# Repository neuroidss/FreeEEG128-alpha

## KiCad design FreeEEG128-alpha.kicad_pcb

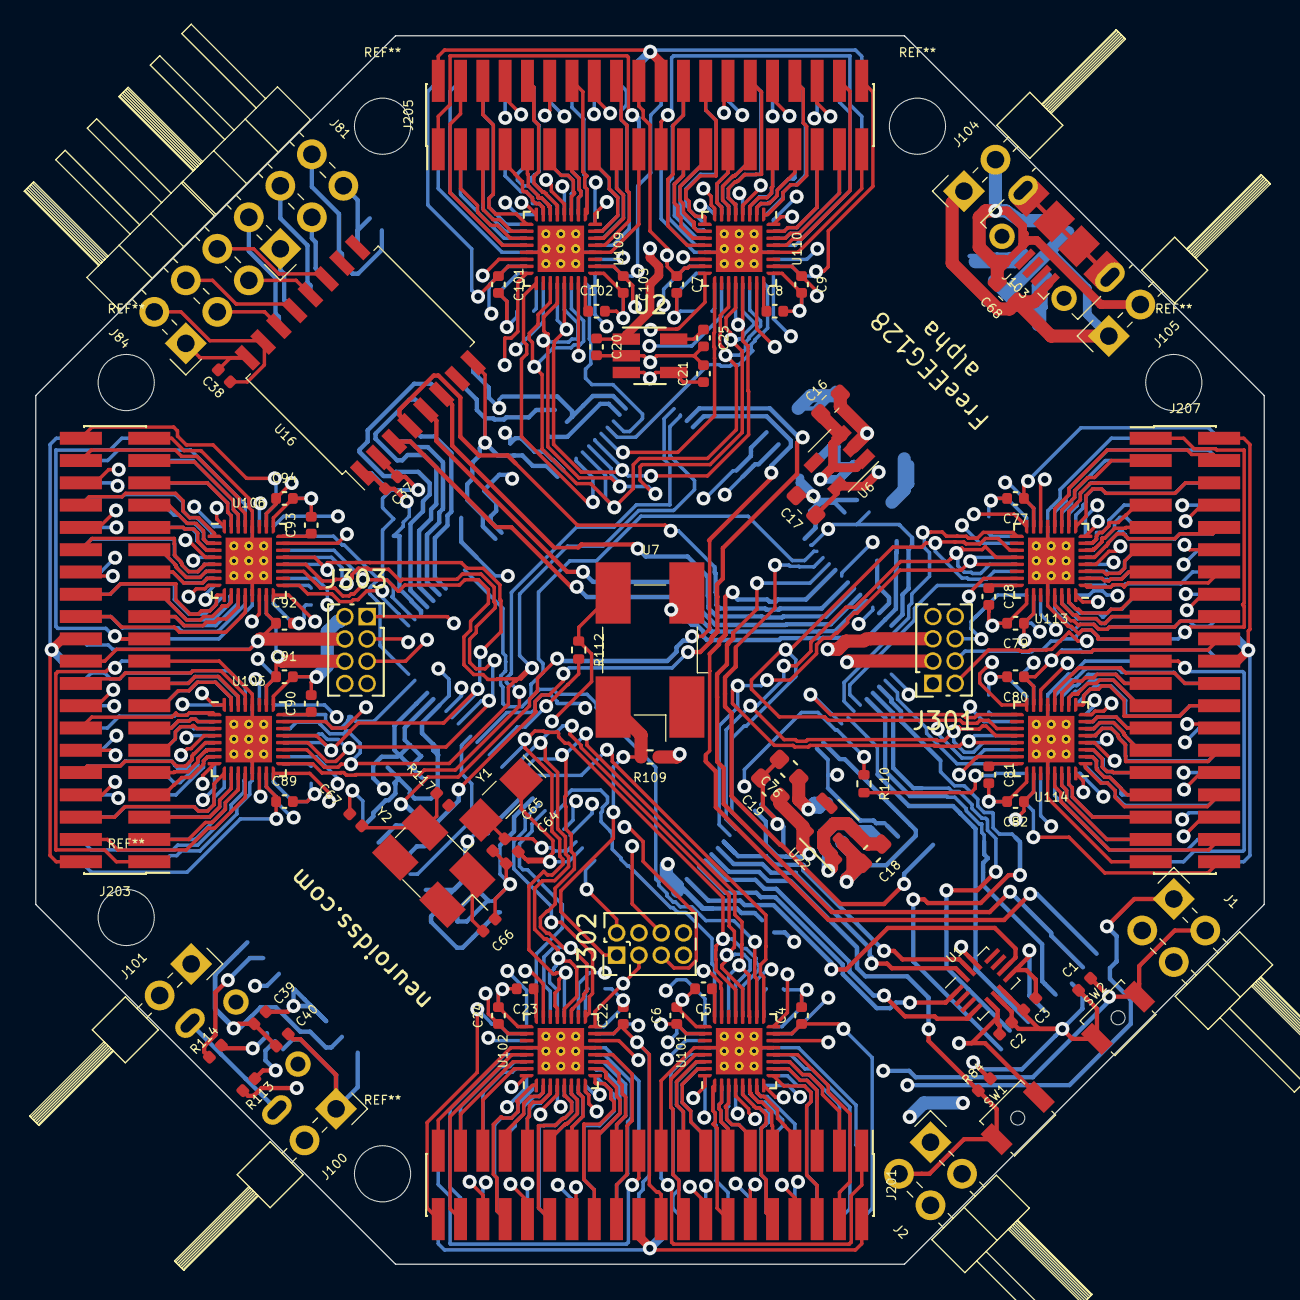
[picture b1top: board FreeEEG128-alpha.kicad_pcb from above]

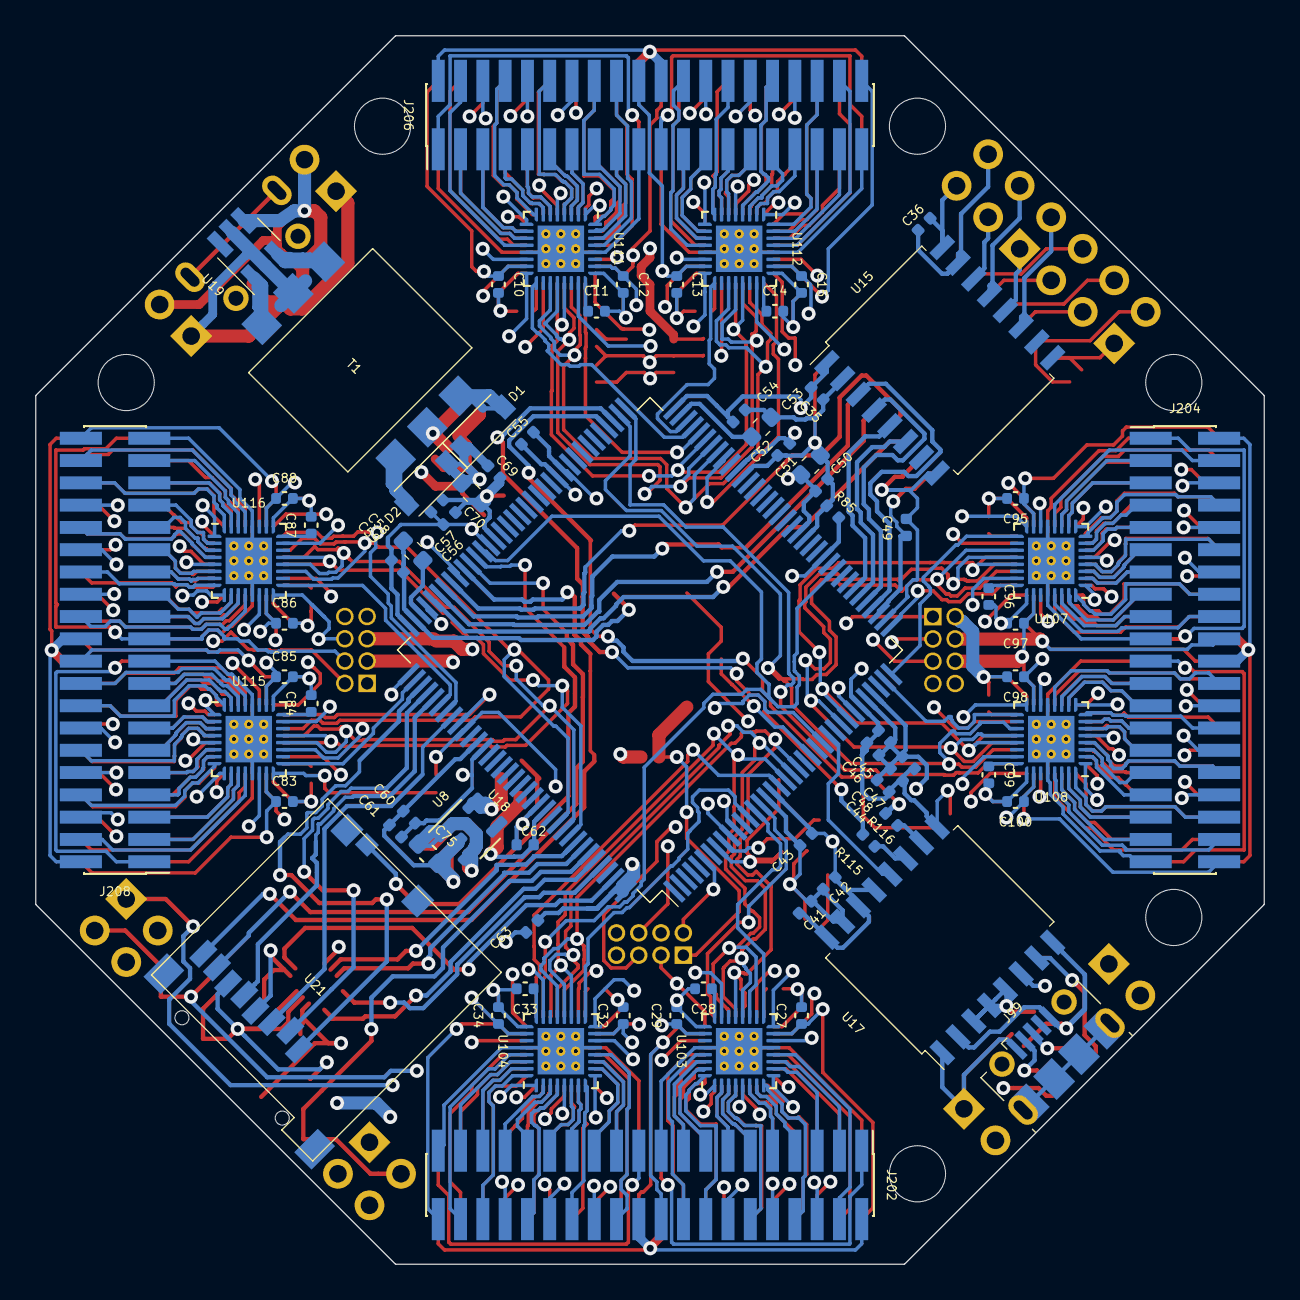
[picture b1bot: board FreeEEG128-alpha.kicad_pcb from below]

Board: 4 copper layers, 70.0 x 70.0 mm, 162 parts (77 on the bottom side), 379 nets.

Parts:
C1, C2, C3, C20, C21, C25, C35, C36, C37, C38, C39, C40, C41, C42, C43, C44, C45, C47, C49, C50, C52, C54, C55, C56, C59, C60, C62, C63, C69: 100n; C_0402_1005Metric
C4, C6, C7, C9, C10, C12, C13, C15, C22, C24, C27, C29, C32, C34, C46, C48, C57, C61, C77, C79, C80, C82, C83, C85, C86, C88, C89, C91, C92, C94, C95, C97, C98, C100, C101, C103: 1u; C_0402_1005Metric
C5, C8, C11, C14, C23, C28, C33, C78, C81, C84, C87, C90, C93, C96, C99, C102: 220nF; C_0402_1005Metric
C16, C17, C18, C19, C53, C58, C75, C76: 2.2u; C_0603_1608Metric
C51: 4.7u; C_0603_1608Metric
C64, C66: CL1; C_0402_1005Metric
C65, C67: CL2; C_0402_1005Metric
C68, C70: 10u; C_0603_1608Metric
D1, D2: D_Schottky; D_SOD-123
J1, J2: Conn_02x02_Odd_Even; PinHeader_2x02_P2.54mm_Horizontal
J81, J84: Conn_02x03_Odd_Even; PinHeader_2x03_P2.54mm_Horizontal
J99, J103: USB_B_Micro; USB_Micro-B_Molex-105017-0001
J100, J101, J104, J105: Conn_01x02; PinHeader_2x01_P2.54mm_Horizontal
J201, J202, J203, J204, J205, J206, J207, J208: Conn_02x20_Odd_Even; PinHeader_2x20_P1.27mm_Vertical_SMD
J301, J303: Conn_02x04_Odd_Even; PinSocket_2x04_P1.27mm_Vertical
J302: Conn_02x04_Odd_Even; PinHeader_2x04_P1.27mm_Vertical
R84, R85: 4k7; R_0402_1005Metric
R109, R110, R112: 0; R_0402_1005Metric
R113, R114, R115, R116: 24; R_0402_1005Metric
R117: R_EXT; R_0402_1005Metric
SW1, SW2: SW_Push; SW_SPST_B3U-1000P-B
T1: 750315371
U1: LSM6DS3; Bosch_LGA-14_3x2.5mm_P0.5mm
U2: REF2025; SOT-23-5_HandSoldering
U6, U8, U22: LP5907; SOT-23-5
U7: FXO-SM7_OSC-SMD7050_short; Oscillator_SMD_EuroQuartz_XO91-4Pin_7.0x5.0mm_HandSoldering
U15: ISO7341c; SOIC-16W_7.5x10.3mm_P1.27mm
U16: ADUM1402BRWZ; SOIC-16W_7.5x10.3mm_P1.27mm
U17: ADuM3160; SOIC-16W_7.5x10.3mm_P1.27mm
U18: STM32H743ZITx; LQFP-144_20x20mm_P0.5mm
U19: SN6505B; SOT-23-6_Handsoldering
U21: 473521001
U101, U102, U103, U104, U105, U106, U107, U108, U109, U110, U111, U112, U113, U114, U115, U116: ADS131M08IRSN; QFN-32-1EP_4x4mm_P0.4mm_EP2.65x2.65mm_ThermalVias
Y1: 32768Hz; Crystal_SMD_EuroQuartz_EQ161-2Pin_3.2x1.5mm_HandSoldering
Y2: 16MHz; Crystal_SMD_EuroQuartz_MJ-4Pin_5.0x3.2mm_HandSoldering

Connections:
/ADC1/24_CAP: C5.1, U101.24 (CAP)
/ADC2/24_CAP: C23.1, U102.24 (CAP)
/ADC3/24_CAP: C28.1, U103.24 (CAP)
/ADC4/24_CAP: C33.1, U104.24 (CAP)
/ADC5/24_CAP: C90.1, U105.24 (CAP)
/ADC6/24_CAP: C93.1, U106.24 (CAP)
/ADC7/24_CAP: C96.1, U107.24 (CAP)
/ADC8/24_CAP: C99.1, U108.24 (CAP)
/ADC9/24_CAP: C102.1, U109.24 (CAP)
/ADC10/24_CAP: C8.1, U110.24 (CAP)
/ADC11/24_CAP: C11.1, U111.24 (CAP)
/ADC12/24_CAP: C14.1, U112.24 (CAP)
/ADC13/24_CAP: C78.1, U113.24 (CAP)
/ADC14/24_CAP: C81.1, U114.24 (CAP)
/ADC15/24_CAP: C84.1, U115.24 (CAP)
/ADC16/24_CAP: C87.1, U116.24 (CAP)
/MCU/8_PC14: C64.1, U18.8 (PC14), Y1.1
/MCU/9_PC15: C65.1, U18.9 (PC15), Y1.2
/MCU/71_VCAP_1: C53.1, U18.71 (VCAP1)
/MCU/106_VCAP_2: C58.1, U18.106 (VCAP2)
ACC_1_SDO_SAO: U1.1 (SDO/SA0), U18.140 (PB9)
ACC_4_INT1: U1.4 (INT1), U18.139 (PB8)
ACC_6_GND: C1.1, C2.2, C3.2, C4.2, C5.2, C6.2, C7.2, C8.2, C9.2, C10.2, C11.2, C12.2, C13.2, C14.2, C15.2, C16.2, C17.2, C18.2, C19.2, C20.2, C21.2, C22.2, C23.2, C24.2, C25.2, C27.2, C28.2, C29.2, C32.2, C33.2, C34.2, C35.2, C37.2, C41.2, C42.2, C43.2, C44.2, C45.2, C46.2, C47.2, C48.2, C49.2, C50.2, C51.2, C52.2, C53.2, C54.2, C55.2, C56.2, C57.2, C58.2, C59.2, C60.2, C61.2, C62.2, C63.2, C64.2, C65.2, C66.2, C67.2, C69.2, C70.2, C75.2, C76.2, C77.2, C78.2, C79.2, C80.2, C81.2, C82.2, C83.2, C84.2, C85.2, C86.2, C87.2, C88.2, C89.2, C90.2, C91.2, C92.2, C93.2, C94.2, C95.2, C96.2, C97.2, C98.2, C99.2, C100.2, C101.2, C102.2, C103.2, J2.2, J201.19, J201.39, J202.19, J202.39, J203.19, J203.39, J204.19, J204.39, J205.19, J205.39, J206.19, J206.39, J207.19, J207.39, J208.19, J208.39, J301.1, J303.2, R84.2, R85.2, SW2.1, T1.5, U1.6 (GND), U1.7 (GND), U2.2 (GND), U6.2 (GND), U7.2 (GND), U8.2 (GND), U15.2 (GND1), U15.8 (GND1), U16.2 (GND1), U16.8 (GND1), U17.9 (GND2), U17.15 (GND2), U18.16 (VSS), U18.31 (VSSA), U18.38 (VSS), U18.51 (VSS), U18.61 (VSS), U18.83 (VSS), U18.94 (VSS), U18.107 (VSS), U18.120 (VSS), U18.130 (VSS), U21.6 (Vss), U22.2 (GND), U101.13 (AGND), U101.25 (DGND), U101.28 (AGND), U101.33 (Thermal_pad), U102.13 (AGND), U102.25 (DGND), U102.28 (AGND), U102.33 (Thermal_pad), U103.13 (AGND), U103.25 (DGND), U103.28 (AGND), U103.33 (Thermal_pad), U104.13 (AGND), U104.25 (DGND), U104.28 (AGND), U104.33 (Thermal_pad), U105.13 (AGND), U105.25 (DGND), U105.28 (AGND), U105.33 (Thermal_pad), U106.13 (AGND), U106.25 (DGND), U106.28 (AGND), U106.33 (Thermal_pad), U107.13 (AGND), U107.25 (DGND), U107.28 (AGND), U107.33 (Thermal_pad), U108.13 (AGND), U108.25 (DGND), U108.28 (AGND), U108.33 (Thermal_pad), U109.13 (AGND), U109.25 (DGND), U109.28 (AGND), U109.33 (Thermal_pad), U110.13 (AGND), U110.25 (DGND), U110.28 (AGND), U110.33 (Thermal_pad), U111.13 (AGND), U111.25 (DGND), U111.28 (AGND), U111.33 (Thermal_pad), U112.13 (AGND), U112.25 (DGND), U112.28 (AGND), U112.33 (Thermal_pad), U113.13 (AGND), U113.25 (DGND), U113.28 (AGND), U113.33 (Thermal_pad), U114.13 (AGND), U114.25 (DGND), U114.28 (AGND), U114.33 (Thermal_pad), U115.13 (AGND), U115.25 (DGND), U115.28 (AGND), U115.33 (Thermal_pad), U116.13 (AGND), U116.25 (DGND), U116.28 (AGND), U116.33 (Thermal_pad)
ACC_9_INT2: U1.9 (INT2), U18.142 (PE1)
ACC_12_CS: C2.1, C3.1, C19.1, C35.1, C37.1, C41.1, C42.1, C43.1, C44.1, C45.1, C46.1, C47.1, C48.1, C49.1, C50.1, C51.1, C52.1, C54.1, C55.1, C56.1, C57.1, C59.1, C60.1, C61.1, C62.1, C63.1, J2.1, J301.5, J302.2, R109.1, SW1.1, U1.5 (VDDIO), U1.8 (VDD), U1.12 (CS), U15.1 (VCC1), U16.1 (VCC1), U17.13 (SPD), U17.14 (VDD2), U17.16 (VBUS2), U18.6 (VBAT), U18.17 (VDD), U18.30 (VDD), U18.32 (VREF+), U18.33 (VDDA), U18.39 (VDD), U18.52 (VDD), U18.62 (VDD), U18.72 (VDD), U18.84 (VDD), U18.95 (VDD33_USB), U18.108 (VDD), U18.121 (VDD), U18.131 (VDD), U18.143 (PDR_ON), U18.144 (VDD), U21.4 (VDD), U22.5 (OUT)
ACC_13_SCL: U1.13 (SCL), U18.136 (PB6)
ACC_14_SDA: U1.14 (SDA), U18.137 (PB7)
ADC1_01_AIN2P: J201.14, U101.1 (AIN2P)
ADC1_02_AIN2N: J201.13, U101.2 (AIN2N)
ADC1_03_AIN3N: J201.11, U101.3 (AIN3N)
ADC1_04_AIN3P: J201.12, U101.4 (AIN3P)
ADC1_05_AIN4P: J201.10, U101.5 (AIN4P)
ADC1_06_AIN4N: J201.9, U101.6 (AIN4N)
ADC1_07_AIN5N: J201.7, U101.7 (AIN5N)
ADC1_08_AIN5P: J201.8, U101.8 (AIN5P)
ADC1_09_AIN6P: J201.6, U101.9 (AIN6P)
ADC1_10_AIN6N: J201.5, U101.10 (AIN6N)
ADC1_11_AIN7N: J201.3, U101.11 (AIN7N)
ADC1_12_AIN7P: J201.4, U101.12 (AIN7P)
ADC1_17_CS: U18.18 (PF6), U101.17 (CS)
ADC1_18_DRDY: U18.46 (PB0), U18.96 (PC6), U101.18 (DRDY)
ADC1_19_SCLK: U18.19 (PF7), U101.19 (SCLK), U102.19 (SCLK), U103.19 (SCLK), U104.19 (SCLK)
ADC1_20_DOUT: U18.20 (PF8), U101.20 (DOUT), U102.20 (DOUT), U103.20 (DOUT), U104.20 (DOUT)
ADC1_21_DIN: U18.21 (PF9), U101.21 (DIN), U102.21 (DIN), U103.21 (DIN), U104.21 (DIN)
ADC1_29_AIN0P: J201.18, U101.29 (AIN0P)
ADC1_30_AIN0N: J201.17, U101.30 (AIN0N)
ADC1_31_AIN1N: J201.15, U101.31 (AIN1N)
ADC1_32_AIN1P: J201.16, U101.32 (AIN1P)
ADC2_01_AIN2P: J201.34, U102.1 (AIN2P)
ADC2_02_AIN2N: J201.33, U102.2 (AIN2N)
ADC2_03_AIN3N: J201.31, U102.3 (AIN3N)
ADC2_04_AIN3P: J201.32, U102.4 (AIN3P)
ADC2_05_AIN4P: J201.30, U102.5 (AIN4P)
ADC2_06_AIN4N: J201.29, U102.6 (AIN4N)
ADC2_07_AIN5N: J201.27, U102.7 (AIN5N)
ADC2_08_AIN5P: J201.28, U102.8 (AIN5P)
ADC2_09_AIN6P: J201.26, U102.9 (AIN6P)
ADC2_10_AIN6N: J201.25, U102.10 (AIN6N)
ADC2_11_AIN7N: J201.23, U102.11 (AIN7N)
ADC2_12_AIN7P: J201.24, U102.12 (AIN7P)
ADC2_17_CS: U18.15 (PF5), U102.17 (CS)
ADC2_29_AIN0P: J201.38, U102.29 (AIN0P)
ADC2_30_AIN0N: J201.37, U102.30 (AIN0N)
ADC2_31_AIN1N: J201.35, U102.31 (AIN1N)
ADC2_32_AIN1P: J201.36, U102.32 (AIN1P)
ADC3_01_AIN2P: J202.14, U103.1 (AIN2P)
ADC3_02_AIN2N: J202.13, U103.2 (AIN2N)
ADC3_03_AIN3N: J202.11, U103.3 (AIN3N)
ADC3_04_AIN3P: J202.12, U103.4 (AIN3P)
ADC3_05_AIN4P: J202.10, U103.5 (AIN4P)
ADC3_06_AIN4N: J202.9, U103.6 (AIN4N)
ADC3_07_AIN5N: J202.7, U103.7 (AIN5N)
ADC3_08_AIN5P: J202.8, U103.8 (AIN5P)
ADC3_09_AIN6P: J202.6, U103.9 (AIN6P)
ADC3_10_AIN6N: J202.5, U103.10 (AIN6N)
ADC3_11_AIN7N: J202.3, U103.11 (AIN7N)
ADC3_12_AIN7P: J202.4, U103.12 (AIN7P)
ADC3_17_CS: U18.14 (PF4), U103.17 (CS)
ADC3_29_AIN0P: J202.18, U103.29 (AIN0P)
ADC3_30_AIN0N: J202.17, U103.30 (AIN0N)
ADC3_31_AIN1N: J202.15, U103.31 (AIN1N)
ADC3_32_AIN1P: J202.16, U103.32 (AIN1P)
ADC4_01_AIN2P: J202.34, U104.1 (AIN2P)
ADC4_02_AIN2N: J202.33, U104.2 (AIN2N)
ADC4_03_AIN3N: J202.31, U104.3 (AIN3N)
ADC4_04_AIN3P: J202.32, U104.4 (AIN3P)
ADC4_05_AIN4P: J202.30, U104.5 (AIN4P)
ADC4_06_AIN4N: J202.29, U104.6 (AIN4N)
ADC4_07_AIN5N: J202.27, U104.7 (AIN5N)
ADC4_08_AIN5P: J202.28, U104.8 (AIN5P)
ADC4_09_AIN6P: J202.26, U104.9 (AIN6P)
ADC4_10_AIN6N: J202.25, U104.10 (AIN6N)
ADC4_11_AIN7N: J202.23, U104.11 (AIN7N)
ADC4_12_AIN7P: J202.24, U104.12 (AIN7P)
ADC4_17_CS: U18.13 (PF3), U104.17 (CS)
ADC4_29_AIN0P: J202.38, U104.29 (AIN0P)
ADC4_30_AIN0N: J202.37, U104.30 (AIN0N)
ADC4_31_AIN1N: J202.35, U104.31 (AIN1N)
ADC4_32_AIN1P: J202.36, U104.32 (AIN1P)
ADC5_01_AIN2P: J203.14, U105.1 (AIN2P)
ADC5_02_AIN2N: J203.13, U105.2 (AIN2N)
ADC5_03_AIN3N: J203.11, U105.3 (AIN3N)
ADC5_04_AIN3P: J203.12, U105.4 (AIN3P)
ADC5_05_AIN4P: J203.10, U105.5 (AIN4P)
ADC5_06_AIN4N: J203.9, U105.6 (AIN4N)
ADC5_07_AIN5N: J203.7, U105.7 (AIN5N)
ADC5_08_AIN5P: J203.8, U105.8 (AIN5P)
ADC5_09_AIN6P: J203.6, U105.9 (AIN6P)
ADC5_10_AIN6N: J203.5, U105.10 (AIN6N)
ADC5_11_AIN7N: J203.3, U105.11 (AIN7N)
ADC5_12_AIN7P: J203.4, U105.12 (AIN7P)
ADC5_17_CS: U18.73 (PB12), U105.17 (CS)
ADC5_19_SCLK: U18.74 (PB13), U105.19 (SCLK), U106.19 (SCLK), U107.19 (SCLK), U108.19 (SCLK)
ADC5_20_DOUT: U18.28 (PC2_C), U105.20 (DOUT), U106.20 (DOUT), U107.20 (DOUT), U108.20 (DOUT)
ADC5_21_DIN: U18.29 (PC3_C), U105.21 (DIN), U106.21 (DIN), U107.21 (DIN), U108.21 (DIN)
ADC5_29_AIN0P: J203.18, U105.29 (AIN0P)
ADC5_30_AIN0N: J203.17, U105.30 (AIN0N)
ADC5_31_AIN1N: J203.15, U105.31 (AIN1N)
ADC5_32_AIN1P: J203.16, U105.32 (AIN1P)
ADC6_01_AIN2P: J203.34, U106.1 (AIN2P)
ADC6_02_AIN2N: J203.33, U106.2 (AIN2N)
ADC6_03_AIN3N: J203.31, U106.3 (AIN3N)
ADC6_04_AIN3P: J203.32, U106.4 (AIN3P)
ADC6_05_AIN4P: J203.30, U106.5 (AIN4P)
ADC6_06_AIN4N: J203.29, U106.6 (AIN4N)
ADC6_07_AIN5N: J203.27, U106.7 (AIN5N)
ADC6_08_AIN5P: J203.28, U106.8 (AIN5P)
ADC6_09_AIN6P: J203.26, U106.9 (AIN6P)
ADC6_10_AIN6N: J203.25, U106.10 (AIN6N)
ADC6_11_AIN7N: J203.23, U106.11 (AIN7N)
ADC6_12_AIN7P: J203.24, U106.12 (AIN7P)
ADC6_17_CS: U18.37 (PA3), U106.17 (CS)
ADC6_29_AIN0P: J203.38, U106.29 (AIN0P)
ADC6_30_AIN0N: J203.37, U106.30 (AIN0N)
ADC6_31_AIN1N: J203.35, U106.31 (AIN1N)
ADC6_32_AIN1P: J203.36, U106.32 (AIN1P)
ADC7_01_AIN2P: J204.14, U107.1 (AIN2P)
ADC7_02_AIN2N: J204.13, U107.2 (AIN2N)
ADC7_03_AIN3N: J204.11, U107.3 (AIN3N)
ADC7_04_AIN3P: J204.12, U107.4 (AIN3P)
ADC7_05_AIN4P: J204.10, U107.5 (AIN4P)
ADC7_06_AIN4N: J204.9, U107.6 (AIN4N)
ADC7_07_AIN5N: J204.7, U107.7 (AIN5N)
ADC7_08_AIN5P: J204.8, U107.8 (AIN5P)
ADC7_09_AIN6P: J204.6, U107.9 (AIN6P)
ADC7_10_AIN6N: J204.5, U107.10 (AIN6N)
ADC7_11_AIN7N: J204.3, U107.11 (AIN7N)
ADC7_12_AIN7P: J204.4, U107.12 (AIN7P)
ADC7_17_CS: U18.36 (PA2), U107.17 (CS)
ADC7_29_AIN0P: J204.18, U107.29 (AIN0P)
ADC7_30_AIN0N: J204.17, U107.30 (AIN0N)
ADC7_31_AIN1N: J204.15, U107.31 (AIN1N)
ADC7_32_AIN1P: J204.16, U107.32 (AIN1P)
ADC8_01_AIN2P: J204.34, U108.1 (AIN2P)
ADC8_02_AIN2N: J204.33, U108.2 (AIN2N)
ADC8_03_AIN3N: J204.31, U108.3 (AIN3N)
ADC8_04_AIN3P: J204.32, U108.4 (AIN3P)
ADC8_05_AIN4P: J204.30, U108.5 (AIN4P)
ADC8_06_AIN4N: J204.29, U108.6 (AIN4N)
ADC8_07_AIN5N: J204.27, U108.7 (AIN5N)
ADC8_08_AIN5P: J204.28, U108.8 (AIN5P)
ADC8_09_AIN6P: J204.26, U108.9 (AIN6P)
ADC8_10_AIN6N: J204.25, U108.10 (AIN6N)
ADC8_11_AIN7N: J204.23, U108.11 (AIN7N)
ADC8_12_AIN7P: J204.24, U108.12 (AIN7P)
ADC8_17_CS: U18.35 (PA1), U108.17 (CS)
ADC8_29_AIN0P: J204.38, U108.29 (AIN0P)
ADC8_30_AIN0N: J204.37, U108.30 (AIN0N)
ADC8_31_AIN1N: J204.35, U108.31 (AIN1N)
ADC8_32_AIN1P: J204.36, U108.32 (AIN1P)
ADC9_01_AIN2P: J205.14, U109.1 (AIN2P)
ADC9_02_AIN2N: J205.13, U109.2 (AIN2N)
ADC9_03_AIN3N: J205.11, U109.3 (AIN3N)
ADC9_04_AIN3P: J205.12, U109.4 (AIN3P)
ADC9_05_AIN4P: J205.10, U109.5 (AIN4P)
ADC9_06_AIN4N: J205.9, U109.6 (AIN4N)
ADC9_07_AIN5N: J205.7, U109.7 (AIN5N)
ADC9_08_AIN5P: J205.8, U109.8 (AIN5P)
ADC9_09_AIN6P: J205.6, U109.9 (AIN6P)
ADC9_10_AIN6N: J205.5, U109.10 (AIN6N)
ADC9_11_AIN7N: J205.3, U109.11 (AIN7N)
ADC9_12_AIN7P: J205.4, U109.12 (AIN7P)
ADC9_17_CS: U18.64 (PE11), U109.17 (CS)
ADC9_29_AIN0P: J205.18, U109.29 (AIN0P)
ADC9_30_AIN0N: J205.17, U109.30 (AIN0N)
ADC9_31_AIN1N: J205.15, U109.31 (AIN1N)
ADC9_32_AIN1P: J205.16, U109.32 (AIN1P)
ADC10_01_AIN2P: J205.34, U110.1 (AIN2P)
ADC10_02_AIN2N: J205.33, U110.2 (AIN2N)
ADC10_03_AIN3N: J205.31, U110.3 (AIN3N)
ADC10_04_AIN3P: J205.32, U110.4 (AIN3P)
ADC10_05_AIN4P: J205.30, U110.5 (AIN4P)
ADC10_06_AIN4N: J205.29, U110.6 (AIN4N)
ADC10_07_AIN5N: J205.27, U110.7 (AIN5N)
ADC10_08_AIN5P: J205.28, U110.8 (AIN5P)
ADC10_09_AIN6P: J205.26, U110.9 (AIN6P)
ADC10_10_AIN6N: J205.25, U110.10 (AIN6N)
ADC10_11_AIN7N: J205.23, U110.11 (AIN7N)
ADC10_12_AIN7P: J205.24, U110.12 (AIN7P)
ADC10_14_REFIN: C20.1, U2.1 (VBIAS), U101.14 (REFIN), U102.14 (REFIN), U103.14 (REFIN), U104.14 (REFIN), U105.14 (REFIN), U106.14 (REFIN), U107.14 (REFIN), U108.14 (REFIN), U109.14 (REFIN), U110.14 (REFIN), U111.14 (REFIN), U112.14 (REFIN), U113.14 (REFIN), U114.14 (REFIN), U115.14 (REFIN), U116.14 (REFIN)
ADC10_15_AVDD: C4.1, C7.1, C10.1, C13.1, C17.1, C22.1, C27.1, C32.1, C77.1, C80.1, C83.1, C86.1, C89.1, C92.1, C95.1, C98.1, C101.1, J201.20, J201.40, J202.20, J202.40, J203.20, J203.40, J204.20, J204.40, J205.20, J205.40, J206.20, J206.40, J207.20, J207.40, J208.20, J208.40, J303.4, U6.5 (OUT), U101.15 (AVDD), U102.15 (AVDD), U103.15 (AVDD), U104.15 (AVDD), U105.15 (AVDD), U106.15 (AVDD), U107.15 (AVDD), U108.15 (AVDD), U109.15 (AVDD), U110.15 (AVDD), U111.15 (AVDD), U112.15 (AVDD), U113.15 (AVDD), U114.15 (AVDD), U115.15 (AVDD), U116.15 (AVDD)
ADC10_16_SYNC/RESET: J301.6, J302.3, R110.2, U101.16 (SYNC/RESET), U102.16 (SYNC/RESET), U103.16 (SYNC/RESET), U104.16 (SYNC/RESET), U105.16 (SYNC/RESET), U106.16 (SYNC/RESET), U107.16 (SYNC/RESET), U108.16 (SYNC/RESET), U109.16 (SYNC/RESET), U110.16 (SYNC/RESET), U111.16 (SYNC/RESET), U112.16 (SYNC/RESET), U113.16 (SYNC/RESET), U114.16 (SYNC/RESET), U115.16 (SYNC/RESET), U116.16 (SYNC/RESET)
ADC10_17_CS: U18.68 (PE15), U110.17 (CS)
ADC10_19_SCLK: U18.65 (PE12), U109.19 (SCLK), U110.19 (SCLK), U111.19 (SCLK), U112.19 (SCLK)
ADC10_20_DOUT: U18.66 (PE13), U109.20 (DOUT), U110.20 (DOUT), U111.20 (DOUT), U112.20 (DOUT)
ADC10_21_DIN: U18.67 (PE14), U109.21 (DIN), U110.21 (DIN), U111.21 (DIN), U112.21 (DIN)
ADC10_23_XTAL1/CLKIN: U18.100 (PA8), U101.23 (XTAL1/CLKIN), U102.23 (XTAL1/CLKIN), U103.23 (XTAL1/CLKIN), U104.23 (XTAL1/CLKIN), U105.23 (XTAL1/CLKIN), U106.23 (XTAL1/CLKIN), U107.23 (XTAL1/CLKIN), U108.23 (XTAL1/CLKIN), U109.23 (XTAL1/CLKIN), U110.23 (XTAL1/CLKIN), U111.23 (XTAL1/CLKIN), U112.23 (XTAL1/CLKIN), U113.23 (XTAL1/CLKIN), U114.23 (XTAL1/CLKIN), U115.23 (XTAL1/CLKIN), U116.23 (XTAL1/CLKIN)
ADC10_26_DVDD: C6.1, C9.1, C12.1, C15.1, C24.1, C29.1, C34.1, C76.1, C79.1, C82.1, C85.1, C88.1, C91.1, C94.1, C97.1, C100.1, C103.1, J303.6, U8.5 (OUT), U101.26 (DVDD), U102.26 (DVDD), U103.26 (DVDD), U104.26 (DVDD), U105.26 (DVDD), U106.26 (DVDD), U107.26 (DVDD), U108.26 (DVDD), U109.26 (DVDD), U110.26 (DVDD), U111.26 (DVDD), U112.26 (DVDD), U113.26 (DVDD), U114.26 (DVDD), U115.26 (DVDD), U116.26 (DVDD)
ADC10_29_AIN0P: J205.38, U110.29 (AIN0P)
ADC10_30_AIN0N: J205.37, U110.30 (AIN0N)
ADC10_31_AIN1N: J205.35, U110.31 (AIN1N)
ADC10_32_AIN1P: J205.36, U110.32 (AIN1P)
ADC11_01_AIN2P: J206.14, U111.1 (AIN2P)
ADC11_02_AIN2N: J206.13, U111.2 (AIN2N)
ADC11_03_AIN3N: J206.11, U111.3 (AIN3N)
ADC11_04_AIN3P: J206.12, U111.4 (AIN3P)
ADC11_05_AIN4P: J206.10, U111.5 (AIN4P)
ADC11_06_AIN4N: J206.9, U111.6 (AIN4N)
ADC11_07_AIN5N: J206.7, U111.7 (AIN5N)
ADC11_08_AIN5P: J206.8, U111.8 (AIN5P)
ADC11_09_AIN6P: J206.6, U111.9 (AIN6P)
ADC11_10_AIN6N: J206.5, U111.10 (AIN6N)
ADC11_11_AIN7N: J206.3, U111.11 (AIN7N)
ADC11_12_AIN7P: J206.4, U111.12 (AIN7P)
ADC11_17_CS: U18.69 (PB10), U111.17 (CS)
ADC11_29_AIN0P: J206.18, U111.29 (AIN0P)
ADC11_30_AIN0N: J206.17, U111.30 (AIN0N)
ADC11_31_AIN1N: J206.15, U111.31 (AIN1N)
ADC11_32_AIN1P: J206.16, U111.32 (AIN1P)
ADC12_01_AIN2P: J206.34, U112.1 (AIN2P)
ADC12_02_AIN2N: J206.33, U112.2 (AIN2N)
ADC12_03_AIN3N: J206.31, U112.3 (AIN3N)
ADC12_04_AIN3P: J206.32, U112.4 (AIN3P)
ADC12_05_AIN4P: J206.30, U112.5 (AIN4P)
ADC12_06_AIN4N: J206.29, U112.6 (AIN4N)
ADC12_07_AIN5N: J206.27, U112.7 (AIN5N)
ADC12_08_AIN5P: J206.28, U112.8 (AIN5P)
ADC12_09_AIN6P: J206.26, U112.9 (AIN6P)
ADC12_10_AIN6N: J206.25, U112.10 (AIN6N)
ADC12_11_AIN7N: J206.23, U112.11 (AIN7N)
ADC12_12_AIN7P: J206.24, U112.12 (AIN7P)
ADC12_17_CS: U18.70 (PB11), U112.17 (CS)
ADC12_29_AIN0P: J206.38, U112.29 (AIN0P)
ADC12_30_AIN0N: J206.37, U112.30 (AIN0N)
ADC12_31_AIN1N: J206.35, U112.31 (AIN1N)
ADC12_32_AIN1P: J206.36, U112.32 (AIN1P)
ADC13_01_AIN2P: J207.14, U113.1 (AIN2P)
ADC13_02_AIN2N: J207.13, U113.2 (AIN2N)
ADC13_03_AIN3N: J207.11, U113.3 (AIN3N)
ADC13_04_AIN3P: J207.12, U113.4 (AIN3P)
ADC13_05_AIN4P: J207.10, U113.5 (AIN4P)
ADC13_06_AIN4N: J207.9, U113.6 (AIN4N)
ADC13_07_AIN5N: J207.7, U113.7 (AIN5N)
ADC13_08_AIN5P: J207.8, U113.8 (AIN5P)
ADC13_09_AIN6P: J207.6, U113.9 (AIN6P)
ADC13_10_AIN6N: J207.5, U113.10 (AIN6N)
ADC13_11_AIN7N: J207.3, U113.11 (AIN7N)
ADC13_12_AIN7P: J207.4, U113.12 (AIN7P)
ADC13_17_CS: U18.115 (PD1), U113.17 (CS)
ADC13_19_SCLK: U18.133 (PB3), U113.19 (SCLK), U114.19 (SCLK), U115.19 (SCLK), U116.19 (SCLK)
ADC13_20_DOUT: U18.134 (PB4), U113.20 (DOUT), U114.20 (DOUT), U115.20 (DOUT), U116.20 (DOUT)
ADC13_21_DIN: U18.135 (PB5), U113.21 (DIN), U114.21 (DIN), U115.21 (DIN), U116.21 (DIN)
ADC13_29_AIN0P: J207.18, U113.29 (AIN0P)
ADC13_30_AIN0N: J207.17, U113.30 (AIN0N)
ADC13_31_AIN1N: J207.15, U113.31 (AIN1N)
ADC13_32_AIN1P: J207.16, U113.32 (AIN1P)
ADC14_01_AIN2P: J207.34, U114.1 (AIN2P)
ADC14_02_AIN2N: J207.33, U114.2 (AIN2N)
ADC14_03_AIN3N: J207.31, U114.3 (AIN3N)
ADC14_04_AIN3P: J207.32, U114.4 (AIN3P)
ADC14_05_AIN4P: J207.30, U114.5 (AIN4P)
ADC14_06_AIN4N: J207.29, U114.6 (AIN4N)
ADC14_07_AIN5N: J207.27, U114.7 (AIN5N)
ADC14_08_AIN5P: J207.28, U114.8 (AIN5P)
ADC14_09_AIN6P: J207.26, U114.9 (AIN6P)
ADC14_10_AIN6N: J207.25, U114.10 (AIN6N)
ADC14_11_AIN7N: J207.23, U114.11 (AIN7N)
ADC14_12_AIN7P: J207.24, U114.12 (AIN7P)
ADC14_17_CS: U18.117 (PD3), U114.17 (CS)
ADC14_29_AIN0P: J207.38, U114.29 (AIN0P)
ADC14_30_AIN0N: J207.37, U114.30 (AIN0N)
ADC14_31_AIN1N: J207.35, U114.31 (AIN1N)
ADC14_32_AIN1P: J207.36, U114.32 (AIN1P)
ADC15_01_AIN2P: J208.14, U115.1 (AIN2P)
ADC15_02_AIN2N: J208.13, U115.2 (AIN2N)
ADC15_03_AIN3N: J208.11, U115.3 (AIN3N)
ADC15_04_AIN3P: J208.12, U115.4 (AIN3P)
ADC15_05_AIN4P: J208.10, U115.5 (AIN4P)
ADC15_06_AIN4N: J208.9, U115.6 (AIN4N)
ADC15_07_AIN5N: J208.7, U115.7 (AIN5N)
ADC15_08_AIN5P: J208.8, U115.8 (AIN5P)
ADC15_09_AIN6P: J208.6, U115.9 (AIN6P)
ADC15_10_AIN6N: J208.5, U115.10 (AIN6N)
ADC15_11_AIN7N: J208.3, U115.11 (AIN7N)
ADC15_12_AIN7P: J208.4, U115.12 (AIN7P)
ADC15_17_CS: U18.110 (PA15), U115.17 (CS)
ADC15_29_AIN0P: J208.18, U115.29 (AIN0P)
ADC15_30_AIN0N: J208.17, U115.30 (AIN0N)
ADC15_31_AIN1N: J208.15, U115.31 (AIN1N)
ADC15_32_AIN1P: J208.16, U115.32 (AIN1P)
ADC16_01_AIN2P: J208.34, U116.1 (AIN2P)
ADC16_02_AIN2N: J208.33, U116.2 (AIN2N)
ADC16_03_AIN3N: J208.31, U116.3 (AIN3N)
ADC16_04_AIN3P: J208.32, U116.4 (AIN3P)
ADC16_05_AIN4P: J208.30, U116.5 (AIN4P)
ADC16_06_AIN4N: J208.29, U116.6 (AIN4N)
ADC16_07_AIN5N: J208.27, U116.7 (AIN5N)
ADC16_08_AIN5P: J208.28, U116.8 (AIN5P)
ADC16_09_AIN6P: J208.26, U116.9 (AIN6P)
ADC16_10_AIN6N: J208.25, U116.10 (AIN6N)
ADC16_11_AIN7N: J208.23, U116.11 (AIN7N)
ADC16_12_AIN7P: J208.24, U116.12 (AIN7P)
ADC16_17_CS: U18.114 (PD0), U116.17 (CS)
ADC16_29_AIN0P: J208.38, U116.29 (AIN0P)
ADC16_30_AIN0N: J208.37, U116.30 (AIN0N)
ADC16_31_AIN1N: J208.35, U116.31 (AIN1N)
ADC16_32_AIN1P: J208.36, U116.32 (AIN1P)
AINREF+: J201.2, J201.22, J202.2, J202.22, J203.2, J203.22, J204.2, J204.22, J205.2, J205.22, J206.2, J206.22, J207.2, J207.22, J208.2, J208.22, J301.2
AINREF-: J201.1, J201.21, J202.1, J202.21, J203.1, J203.21, J204.1, J204.21, J205.1, J205.21, J206.1, J206.21, J207.1, J207.21, J208.1, J208.21, J301.4
AVDD_1_IN: C16.1, C18.1, C21.1, C69.1, C70.1, C75.1, D1.1 (K), D2.1 (K), J2.4, J301.3, U2.3 (EN), U2.4 (VIN), U6.1 (IN), U6.3 (EN), U8.1 (IN), U8.3 (EN), U22.1 (IN), U22.3 (EN)
CRYSTAL_3_OUT: J302.6, R112.1, U7.3 (OUT)
CRYSTAL_4_Vin: J302.1, R109.2, U7.4 (Vin)
ISO_SPI_3_INA: U15.3 (INA), U18.40 (PA4)
ISO_SPI_4_INB: U15.4 (INB), U18.41 (PA5)
ISO_SPI_5_INC: U15.5 (INC), U18.43 (PA7)
ISO_SPI_6_OUTD: U15.6 (OUTD), U18.42 (PA6)
ISO_SPI_11_IND: J81.2, U15.11 (IND)
ISO_SPI_12_OUTC: J81.1, U15.12 (OUTC)
ISO_SPI_13_OUTB: J81.4, U15.13 (OUTB)
ISO_SPI_14_OUTA: J81.3, U15.14 (OUTA)
ISO_SPI_15_GND2: C36.2, J81.6, U15.15 (GND2)
ISO_SPI_16_VCC2: C36.1, J81.5, U15.16 (VCC2)
ISO_UART_3_INA: U16.3 (INA), U18.104 (PA12)
ISO_UART_4_INB: U16.4 (INB), U18.101 (PA9)
ISO_UART_5_OUTC: U16.5 (OUTC), U18.103 (PA11)
ISO_UART_6_OUTD: U16.6 (OUTD), U18.102 (PA10)
ISO_UART_11_IND: J84.6, U16.11 (IND)
ISO_UART_12_INC: J84.5, U16.12 (INC)
ISO_UART_13_OUTB: J84.4, U16.13 (OUTB)
ISO_UART_14_OUTA: J84.3, U16.14 (OUTA)
ISO_UART_15_GND2: C38.2, J84.2, U16.15 (GND2)
ISO_UART_16_VCC2: C38.1, J84.1, U16.16 (VCC2)
ISO_USB_1_VBUS1: C40.1, J99.1 (VBUS), J100.1, U17.1 (VBUS1)
ISO_USB_2_GND1: C39.2, C40.2, J99.5 (GND), J100.2, U17.2 (GND1), U17.8 (GND1)
ISO_USB_3_VDD1: C39.1, U17.3 (VDD1), U17.4 (PDEN), U17.5 (SPU)
ISO_USB_6_UD–: J99.2 (D-), J101.2, R113.2
ISO_USB_7_UD+: J99.3 (D+), J101.1, R114.2
ISO_USB_10_DD+: R116.1, U18.76 (PB15)
ISO_USB_11_DD–: R115.1, U18.75 (PB14)
ISO_USB_12_PIN: U17.12 (PIN), U18.26 (PC0)
MCU_10_PF0_I2C2_SDA: J303.5, U18.10 (PF0)
MCU_11_PF1_I2C2_SCL: J303.3, U18.11 (PF1)
MCU_23_RCC_OSC_IN: J302.5, J303.1, R112.2, U18.23 (PH0)
MCU_25_NRST: C1.2, J1.2, SW2.2, U18.25 (NRST)
MCU_48_PB2_BOOT1: J1.1, R85.1, U18.48 (PB2)
MCU_97_PC7_SDMMC1_DETECT: U18.97 (PC7), U21.9 (DETECT)
MCU_98_PC8_SDMMC1_D0: U18.98 (PC8), U21.7 (DATA0)
MCU_99_PC9_SDMMC1_D1: U18.99 (PC9), U21.8 (DATA1)
MCU_105_PA13_SYS_JTMS-SWDIO: J1.4, U18.105 (PA13)
MCU_109_PA14_SYS_JTCK-SWCLK: J1.3, U18.109 (PA14)
MCU_111_PC10_SDMMC1_D2: U18.111 (PC10), U21.1 (DATA2)
MCU_112_PC11_SDMMC1_D3: U18.112 (PC11), U21.2 (DATA3)
MCU_113_PC12_SDMMC1_CK: U18.113 (PC12), U21.5 (CLK)
MCU_116_PD2_SDMMC1_CMD: U18.116 (PD2), U21.3 (CMD)
MCU_118_PD4_ADC1_SYNC/RESET: J302.4, R110.1, U18.118 (PD4)
MCU_138_BOOT0: J2.3, R84.1, SW1.2, U18.138 (BOOT0)
unnamed: C66.1, Y2.1
unnamed: C67.1, R117.2, Y2.2
unnamed: D1.2 (A), T1.6
unnamed: D2.2 (A), T1.4
unnamed: R113.1, U17.6 (UD–)
unnamed: R114.1, U17.7 (UD+)
unnamed: R115.2, U17.11 (DD–)
unnamed: R116.2, U17.10 (DD+)
unnamed: T1.1, U19.3 (D2)
unnamed: T1.3, U19.1 (D1)
POWER_1_GND: C68.1, J103.5 (GND), J104.2, J105.2, U19.4 (GND)
POWER_2_VCC: C68.2, J103.1 (VBUS), J104.1, J105.1, T1.2, U19.2 (VCC), U19.5 (EN)
VREF_5_VREF: C25.1, U2.5 (VREF)

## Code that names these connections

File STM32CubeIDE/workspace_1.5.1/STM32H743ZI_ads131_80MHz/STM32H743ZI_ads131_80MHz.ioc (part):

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Mcu.Name=STM32H743ZITx
Mcu.Package=LQFP144
Mcu.UserName=STM32H743ZITx
PA0.Signal=SharedStack_PA0
PA0.Stacked=true
PA1.GPIOParameters=PinState,GPIO_Label
PA1.GPIO_Label=SPI2_NSS2
PA1.PinState=GPIO_PIN_SET
PA1.Signal=GPIO_Output
PA10.Mode=Asynchronous
PA10.Signal=USART1_RX
PA11.Signal=USART1_CTS
PA12.Signal=USART1_RTS
PA13\ (JTMS/SWDIO).Mode=Serial_Wire
PA13\ (JTMS/SWDIO).Signal=DEBUG_JTMS-SWDIO
PA14\ (JTCK/SWCLK).Mode=Serial_Wire
PA14\ (JTCK/SWCLK).Signal=DEBUG_JTCK-SWCLK
PA15\ (JTDI).GPIOParameters=GPIO_Speed,PinState,GPIO_PuPd,GPIO_Label,GPIO_ModeDefaultOutputPP
PA15\ (JTDI).GPIO_Label=SPI3_NSS
PA15\ (JTDI).GPIO_ModeDefaultOutputPP=GPIO_MODE_OUTPUT_PP
PA15\ (JTDI).GPIO_PuPd=GPIO_NOPULL
PA15\ (JTDI).GPIO_Speed=GPIO_SPEED_FREQ_LOW
PA15\ (JTDI).PinState=GPIO_PIN_SET
PA15\ (JTDI).Signal=GPIO_Output
PA2.GPIOParameters=PinState,GPIO_Label
PA2.GPIO_Label=SPI2_NSS3
PA2.PinState=GPIO_PIN_SET
PA2.Signal=GPIO_Output
PA3.GPIOParameters=PinState,GPIO_Label
PA3.GPIO_Label=SPI2_NSS4
PA3.PinState=GPIO_PIN_SET
PA3.Signal=GPIO_Output
PA4.GPIOParameters=GPIO_Label
PA4.GPIO_Label=SPI1_NSS
PA4.Mode=NSS_Signal_Hard_Output
PA4.Signal=SPI1_NSS
PA5.Mode=Full_Duplex_Master
PA5.Signal=SPI1_SCK
PA6.Mode=Full_Duplex_Master
PA6.Signal=SPI1_MISO
PA7.Mode=Full_Duplex_Master
PA7.Signal=SPI1_MOSI
PA8.Mode=Clock-out-1
PA8.Signal=RCC_MCO_1
PA9.Mode=Asynchronous
PA9.Signal=USART1_TX
PB0.GPIOParameters=GPIO_Label,GPIO_ModeDefaultEXTI
PB0.GPIO_Label=ADC1_DRDY
PB0.GPIO_ModeDefaultEXTI=GPIO_MODE_IT_FALLING
PB0.Signal=GPXTI0
PB10.GPIOParameters=PinState,GPIO_Label
PB10.GPIO_Label=SPI4_NSS3
PB10.PinState=GPIO_PIN_SET
PB10.Signal=GPIO_Output
PB11.GPIOParameters=PinState,GPIO_Label
PB11.GPIO_Label=SPI4_NSS4
PB11.PinState=GPIO_PIN_SET
PB11.Signal=GPIO_Output
PB12.GPIOParameters=GPIO_Speed,PinState,GPIO_PuPd,GPIO_Label,GPIO_ModeDefaultOutputPP
PB12.GPIO_Label=SPI2_NSS
PB12.GPIO_ModeDefaultOutputPP=GPIO_MODE_OUTPUT_PP
PB12.GPIO_PuPd=GPIO_NOPULL
PB12.GPIO_Speed=GPIO_SPEED_FREQ_LOW
PB12.PinState=GPIO_PIN_SET
PB12.Signal=GPIO_Output
PB13.Mode=Full_Duplex_Master
PB13.Signal=SPI2_SCK
PB14.GPIOParameters=GPIO_Speed
PB14.GPIO_Speed=GPIO_SPEED_FREQ_LOW
PB14.Mode=Device_Only_FS
PB14.Signal=USB_OTG_HS_DM
PB15.GPIOParameters=GPIO_Speed
PB15.GPIO_Speed=GPIO_SPEED_FREQ_LOW
PB15.Mode=Device_Only_FS
PB15.Signal=USB_OTG_HS_DP
PB2.GPIOParameters=GPIO_Label
PB2.GPIO_Label=BOOT1
PB2.Signal=GPIO_Input
PB3\ (JTDO/TRACESWO).Mode=Full_Duplex_Master
PB3\ (JTDO/TRACESWO).Signal=SPI3_SCK
PB4\ (NJTRST).Mode=Full_Duplex_Master
PB4\ (NJTRST).Signal=SPI3_MISO
PB5.Mode=Full_Duplex_Master
PB5.Signal=SPI3_MOSI
PB6.Mode=I2C
PB6.Signal=I2C1_SCL
PB7.Mode=I2C
PB7.Signal=I2C1_SDA
PB8.GPIOParameters=GPIO_Label
PB8.GPIO_Label=ACC_INT1
PB8.Signal=GPXTI8
PB9.GPIOParameters=GPIO_Label
PB9.GPIO_Label=ACC_SDO_SAO
PB9.Signal=GPIO_Output
PC0.GPIOParameters=PinState,GPIO_PuPd,GPIO_Label
PC0.GPIO_Label=ISO_USB_PIN
PC0.GPIO_PuPd=GPIO_PULLUP
PC0.PinState=GPIO_PIN_SET
PC0.Signal=GPIO_Output
PC10.Mode=SD_4_bits_Wide_bus
PC10.Signal=SDMMC1_D2
PC11.Mode=SD_4_bits_Wide_bus
PC11.Signal=SDMMC1_D3
PC12.Mode=SD_4_bits_Wide_bus
PC12.Signal=SDMMC1_CK
PC13.GPIOParameters=GPIO_Label
PC13.GPIO_Label=ADC2_DRDY
PC13.Signal=GPXTI13
PC2_C.Mode=Full_Duplex_Master
PC2_C.Signal=SPI2_MISO
PC3_C.Mode=Full_Duplex_Master
PC3_C.Signal=SPI2_MOSI
PC6.Signal=SharedStack_PC6
PC6.Stacked=true
PC7.GPIOParameters=GPIO_Label
PC7.GPIO_Label=SDMMC1_DETECT
PC7.Signal=GPIO_Input
PC8.Mode=SD_4_bits_Wide_bus
PC8.Signal=SDMMC1_D0
PC9.Mode=SD_4_bits_Wide_bus
PC9.Signal=SDMMC1_D1
PD0.GPIOParameters=PinState,GPIO_Label
PD0.GPIO_Label=SPI3_NSS2
PD0.PinState=GPIO_PIN_SET
PD0.Signal=GPIO_Output
PD1.GPIOParameters=PinState,GPIO_Label
PD1.GPIO_Label=SPI3_NSS3
PD1.PinState=GPIO_PIN_SET
PD1.Signal=GPIO_Output
PD2.Mode=SD_4_bits_Wide_bus
PD2.Signal=SDMMC1_CMD
PD3.GPIOParameters=PinState,GPIO_Label
PD3.GPIO_Label=SPI3_NSS4
PD3.PinState=GPIO_PIN_SET
PD3.Signal=GPIO_Output
PD4.GPIOParameters=GPIO_Label
PD4.GPIO_Label=ADC1_SYNC/RESET
PD4.Signal=GPIO_Output
PE11.GPIOParameters=PinState,GPIO_Label
PE11.GPIO_Label=SPI4_NSS
PE11.PinState=GPIO_PIN_SET
PE11.Signal=GPIO_Output
PE12.Mode=Full_Duplex_Master
PE12.Signal=SPI4_SCK
PE13.Mode=Full_Duplex_Master
PE13.Signal=SPI4_MISO
PE14.Mode=Full_Duplex_Master
PE14.Signal=SPI4_MOSI
PE15.GPIOParameters=PinState,GPIO_Label
PE15.GPIO_Label=SPI4_NSS2
PE15.PinState=GPIO_PIN_SET
PE15.Signal=GPIO_Output
PE7.Signal=S_TIM1_ETR
PE9.Signal=S_TIM1_CH1
PF0.Mode=I2C
PF0.Signal=I2C2_SDA
PF1.Mode=I2C
PF1.Signal=I2C2_SCL
PF10.GPIOParameters=GPIO_Label
PF10.GPIO_Label=ADC3_DRDY
PF10.Signal=GPXTI10
PF3.GPIOParameters=PinState,GPIO_Label
PF3.GPIO_Label=SPI5_NSS4
PF3.PinState=GPIO_PIN_SET
PF3.Signal=GPIO_Output
PF4.GPIOParameters=PinState,GPIO_Label
PF4.GPIO_Label=SPI5_NSS3
PF4.PinState=GPIO_PIN_SET
PF4.Signal=GPIO_Output
PF5.GPIOParameters=PinState,GPIO_Label
PF5.GPIO_Label=SPI5_NSS2
PF5.PinState=GPIO_PIN_SET
PF5.Signal=GPIO_Output
PF6.GPIOParameters=PinState,GPIO_Label
PF6.GPIO_Label=SPI5_NSS
PF6.PinState=GPIO_PIN_SET
PF6.Signal=GPIO_Output
PF7.Mode=Full_Duplex_Master
PF7.Signal=SPI5_SCK
PF8.Mode=Full_Duplex_Master
PF8.Signal=SPI5_MISO
PF9.Mode=Full_Duplex_Master
PF9.Signal=SPI5_MOSI
PG12.Mode=Full_Duplex_Master
PG12.Signal=SPI6_MISO
PG13.Mode=Full_Duplex_Master
PG13.Signal=SPI6_SCK
PG14.Mode=Full_Duplex_Master
PG14.Signal=SPI6_MOSI
PG4.GPIOParameters=GPIO_Label
PG4.GPIO_Label=ADC4_DRDY
PG4.Signal=GPXTI4
PG5.GPIOParameters=GPIO_Label
PG5.GPIO_Label=SPI6_NSS4
PG5.Signal=GPIO_Output
PG6.GPIOParameters=GPIO_Label
PG6.GPIO_Label=SPI6_NSS3
PG6.Signal=GPIO_Output
PG7.GPIOParameters=GPIO_Label
PG7.GPIO_Label=SPI6_NSS2
PG7.Signal=GPIO_Output
PG8.GPIOParameters=GPIO_Label
PG8.GPIO_Label=SPI6_NSS
PG8.Signal=GPIO_Output
PH0-OSC_IN\ (PH0).Mode=HSE-External-Clock-Source
PH0-OSC_IN\ (PH0).Signal=RCC_OSC_IN
RCC.HSE_VALUE=8192000
RCC.SYSCLKFreq_VALUE=80000000
RCC.SYSCLKSource=RCC_SYSCLKSOURCE_PLLCLK
board=custom

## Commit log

2021-09-05 delete
2021-09-05 add stm32cubeide
2021-10-05 shorted, noise
